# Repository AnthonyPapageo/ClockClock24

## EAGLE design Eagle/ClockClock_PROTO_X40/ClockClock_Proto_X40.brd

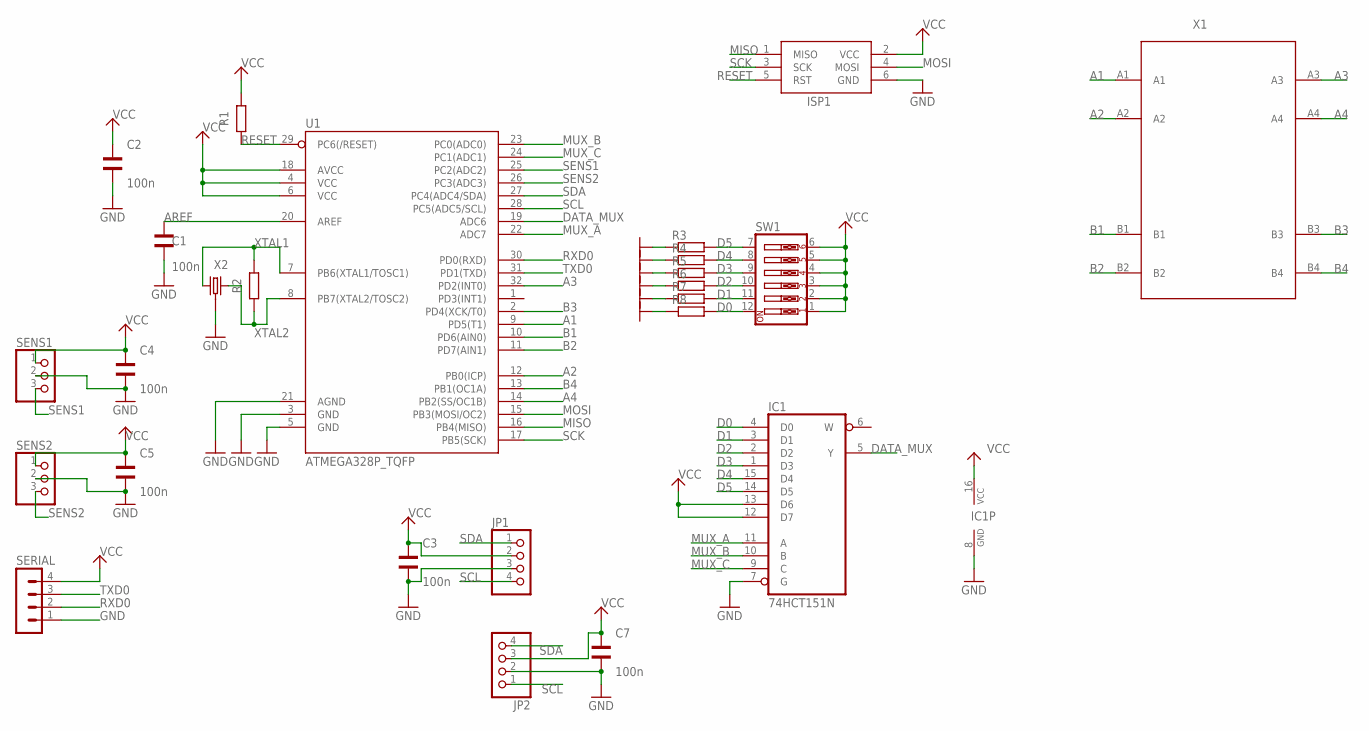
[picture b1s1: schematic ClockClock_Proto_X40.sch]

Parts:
C1, C2, C3, C4, C5, C7: 100n; WCAP-CSMH_1206_WAVE
IC1: 74HCT151N; DIL16
ISP1: AVRISP-6; AVRISP
JP1, JP2: PINHD-1X4/90; 1X04/90
R1: 15k; R1206
R2: 1M; R0805
R3, R4, R5, R6, R7, R8: R-EU_R1206; R1206
SENS1, SENS2: PINHD-1X3; 1X03
SERIAL: MA04-1
SW1: SWITCH_DIP-6_90; DIP6_SWITCH_90DEG
U1: ATMEGA328P_TQFP; TQFP32-08
X1: X40_MOTOR
X2: AEL_ZTT_RESONATOR_16M; AEL_ZTT_RESONATOR

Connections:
A1: U1.9 (PD5(T1)), X1.A1
A2: U1.12 (PB0(ICP)), X1.A2
A3: U1.32 (PD2(INT0)), X1.A3
A4: U1.14 (PB2(SS/OC1B)), X1.A4
AREF: C1.2, U1.20 (AREF)
B1: U1.10 (PD6(AIN0)), X1.B1
B2: U1.11 (PD7(AIN1)), X1.B2
B3: U1.2 (PD4(XCK/T0)), X1.B3
B4: U1.13 (PB1(OC1A)), X1.B4
D0: IC1.4 (D0), R8.2, SW1.12
D1: IC1.3 (D1), R7.2, SW1.11
D2: IC1.2 (D2), R6.2, SW1.10
D3: IC1.1 (D3), R5.2, SW1.9
D4: IC1.15 (D4), R4.2, SW1.8
D5: IC1.14 (D5), R3.2, SW1.7
DATA_MUX: IC1.5 (Y), U1.19 (ADC6)
GND: C1.1, C2.1, C3.1, C4.1, C5.1, C7.1, IC1.7 (G), IC1.8 (GND), ISP1.6 (GND), JP1.3, JP2.2, R3.1, R4.1, R5.1, R6.1, R7.1, R8.1, SENS1.2, SENS2.2, SERIAL.1, U1.3 (GND), U1.5 (GND), U1.21 (AGND), X2.GND
MISO: ISP1.1 (MISO), U1.16 (PB4(MISO))
MOSI: ISP1.4 (MOSI), U1.15 (PB3(MOSI/OC2))
MUX_A: IC1.11 (A), U1.22 (ADC7)
MUX_B: IC1.10 (B), U1.23 (PC0(ADC0))
MUX_C: IC1.9 (C), U1.24 (PC1(ADC1))
RESET: ISP1.5 (RST), R1.1, U1.29 (PC6(/RESET))
RXD0: SERIAL.2, U1.30 (PD0(RXD))
SCK: ISP1.3 (SCK), U1.17 (PB5(SCK))
SCL: JP1.4, JP2.1, U1.28 (PC5(ADC5/SCL))
SDA: JP1.1, JP2.4, U1.27 (PC4(ADC4/SDA))
SENS1: SENS1.3, U1.25 (PC2(ADC2))
SENS2: SENS2.3, U1.26 (PC3(ADC3))
TXD0: SERIAL.3, U1.31 (PD1(TXD))
VCC: C2.2, C3.2, C4.2, C5.2, C7.2, IC1.12 (D7), IC1.13 (D6), IC1.16 (VCC), ISP1.2 (VCC), JP1.2, JP2.3, R1.2, SENS1.1, SENS2.1, SERIAL.4, SW1.1, SW1.2, SW1.3, SW1.4, SW1.5, SW1.6, U1.4 (VCC), U1.6 (VCC), U1.18 (AVCC)
XTAL1: R2.2, U1.7 (PB6(XTAL1/TOSC1)), X2.P$1 (1)
XTAL2: R2.1, U1.8 (PB7(XTAL2/TOSC2)), X2.P$3 (2)

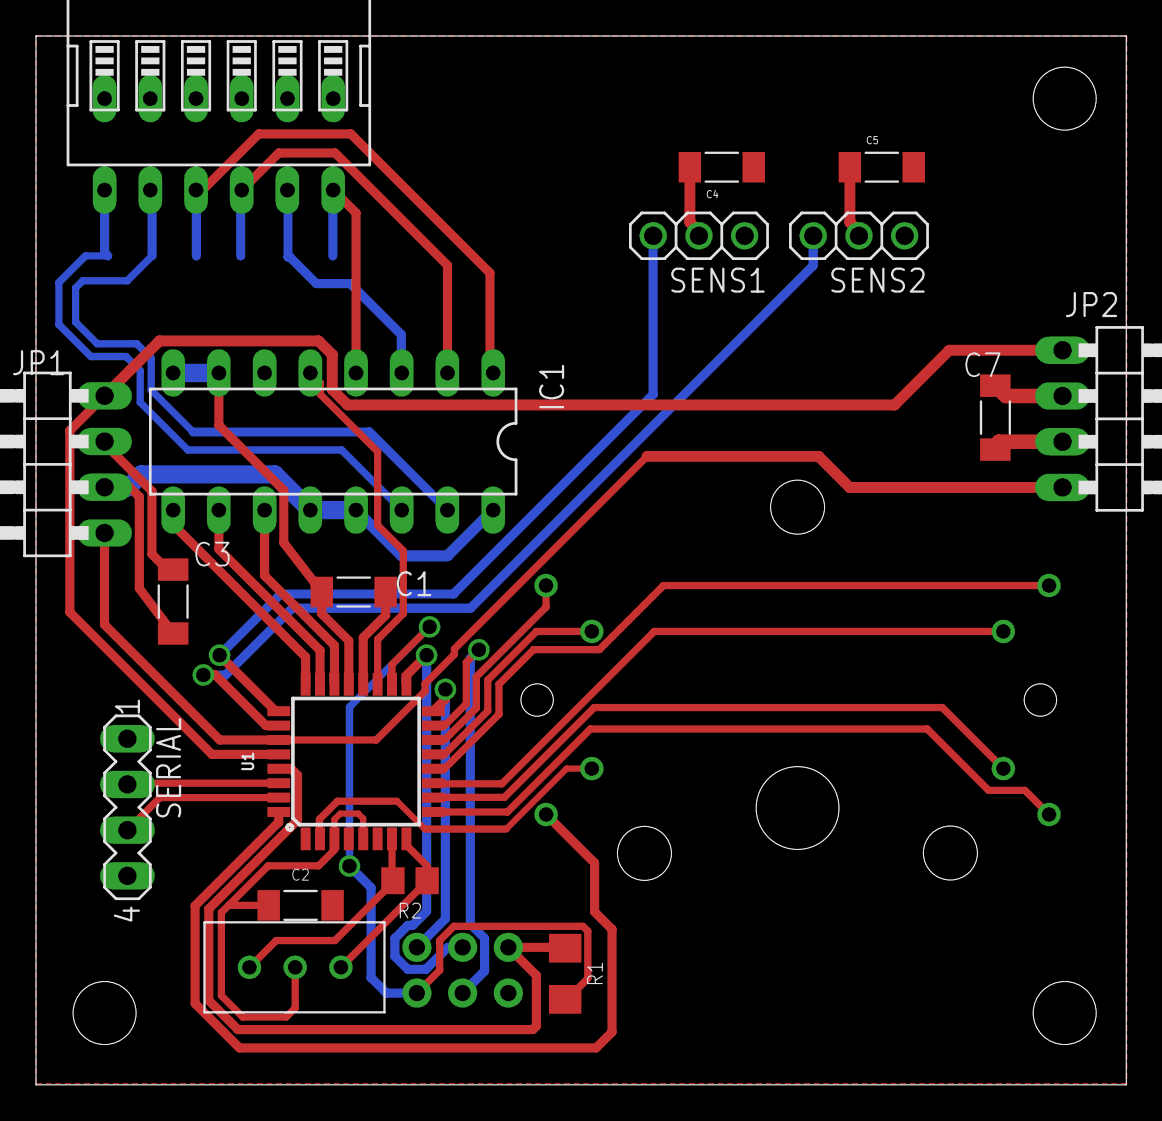
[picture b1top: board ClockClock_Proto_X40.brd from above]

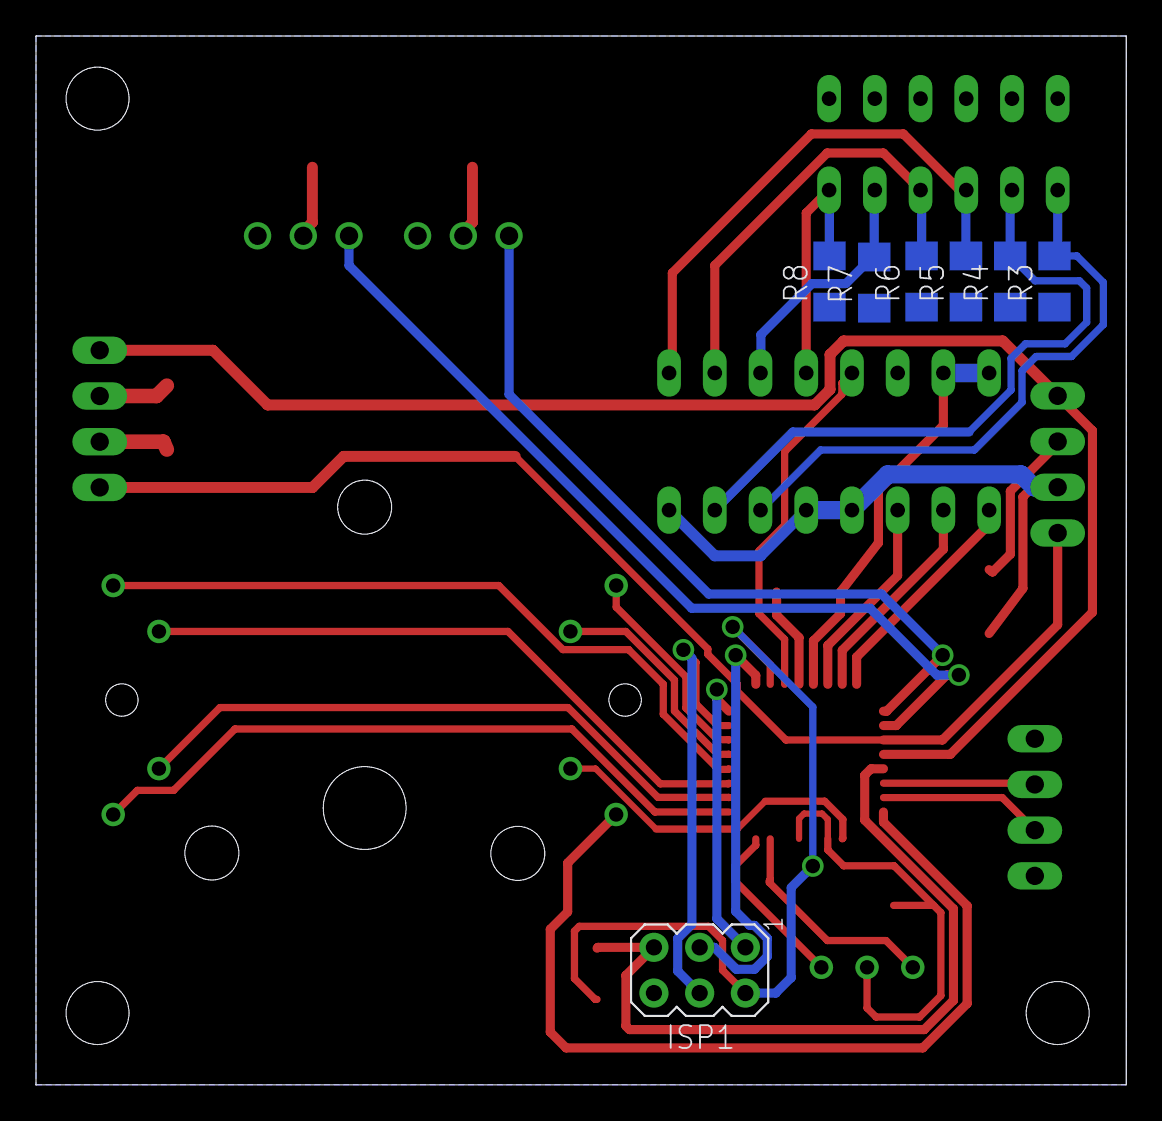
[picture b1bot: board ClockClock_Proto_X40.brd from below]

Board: 2 copper layers, 60.6 x 58.3 mm, 25 parts (7 on the bottom side), 33 nets.

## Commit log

2019-12-15 Added Eagle & STL
2019-12-15 Added Unity project
2019-12-15 Added uC code
2019-12-18 updated unity
2019-12-18 Added iges

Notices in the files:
parts and their libraries:
SparkFun-IC-Microcontroller: Licensing: Creative Commons ShareAlike 4.0 International - https://creativecommons.org/licenses/by-sa/4.0
Wurth_Elektronik_Passive_Capacitors_rev1: Copyright: Würth Elektronik
